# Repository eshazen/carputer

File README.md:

# carputer

Car computer with display and GPS in DIN enclosure

Proposed functions:

* Clock (updated by GPS)
* Nearest town and potentially other geographical features
* Outside temperature

Front panel would have a display, a couple of buttons/knobs
and a USB plug for power from the stereo plus software updates
using Arduino boot loader.

See (Data/README.md)[Data/README.md] for data details and ideas.

## Implementation notes

On the MKR Zero board, there are only a few pins which can be used for
interrupts.  See
[docs](https://docs.arduino.cc/language-reference/en/functions/external-interrupts/attachInterrupt/).
These pins are: 0, 1, 4, 5, 6, 7, 8, 9, A1, A2.

Unfortunately the encoder is connected to 11 and 12.  Pin 7 is unused,
but one interrupt doesn't do the trick.

So far no luck getting timer interrupts to work on the MKR zero.
Best bet seems to be the `Adafruit_ZeroTimer` but even though the
example works it seems to crash when trying to run e.g. SPI after setup.

## User Interface

First version displays 3 lines of nearest towns, with a status
line below with GMT time, GPS status and number of satellites.
Controls not implemented yet.

### Enhancements:

**V3.x**

* Hierarchy of search (state first, then state-specific towns?)
* Simple UI (button/knob to enable/disable debug mode)

**Other**

* Categories of POI, selected by knob
  <br>with timeout to return to town display?
* Clock time in local time zone (how to determine time zone?)
* Analog clock display
* Scrolling of long place names?

## Resources

See [https://github.com/eshazen/town_ident](https://github.com/eshazen/town_ident)
for a preliminary version based on ATMega328.

## Hardware

* **CPU** - Arduino MKR Zero.  SAMD21 cpu with 256k flash and 32k ram.  32-bit M0 core at 48MHz.
* **Display** - OLED with 3.12 inch 256x64 display.  Amazon:  [https://a.co/d/5zJTbLo](https://a.co/d/5zJTbLo)
* **GPS** - NEO-6M module (Amazon: [link](https://a.co/d/gSQQ6ZD).  The NEO-7M is a higher-performance replacement
* **Antenna** - Bingfu Waterproof "Active" GPS antenna SMA (Amazon: [link](https://a.co/d/aN1YYik).

### Display details

Ordered this 3.12" OLED with 16-pin connector from 
Asked ChatGPT for a pinout and it came up with [this](https://chatgpt.com/share/68c1a13d-e6dc-8000-bd67-d93712c7cb28).

Also see [ER-OLEDM028-1_Interfacing.pdf](Docs/ER-OLEDM028-1_Interfacing.pdf).

Link to
[Datasheet](https://newhavendisplay.com/content/specs/NHD-3.12-25664UCY2.pdf) for DigiKey version.

Beeped out from ours

| Function   | Pin |   | Pin | Function   |
|------------|-----|---|-----|------------|
| GND        | 1   |   | 2   | ?VCC       |
| ?          | 3   |   | 4   | D0 (SCLK?) |
| D1 (SDIN?) | 5   |   | 6   | D2         |
| D3         | 7   |   | 8   | D4         |
| D5         | 9   |   | 10  | D6         |
| D7         | 11  |   | 12  | E/RD       |
| R/W        | 13  |   | 14  | DC         |
| RES        | 15  |   | 16  | CS         |
|            |     |   |     |            |

See https://www.hicenda.com/product/312-inch-oled-module-01.html

Finally, referring to a datasheet: https://docs.rs-online.com/6267/0900766b8162af09.pdf
for the display itself with 30 pin flex, we can wring out the pinout with a meter.

Library candidates:

* [SSD1322_for_Adafruit_GFX](https://github.com/venice1200/SSD1322_for_Adafruit_GFX)
* [SSD1322_OLED_library](https://github.com/wjklimek1/SSD1322_OLED_library)

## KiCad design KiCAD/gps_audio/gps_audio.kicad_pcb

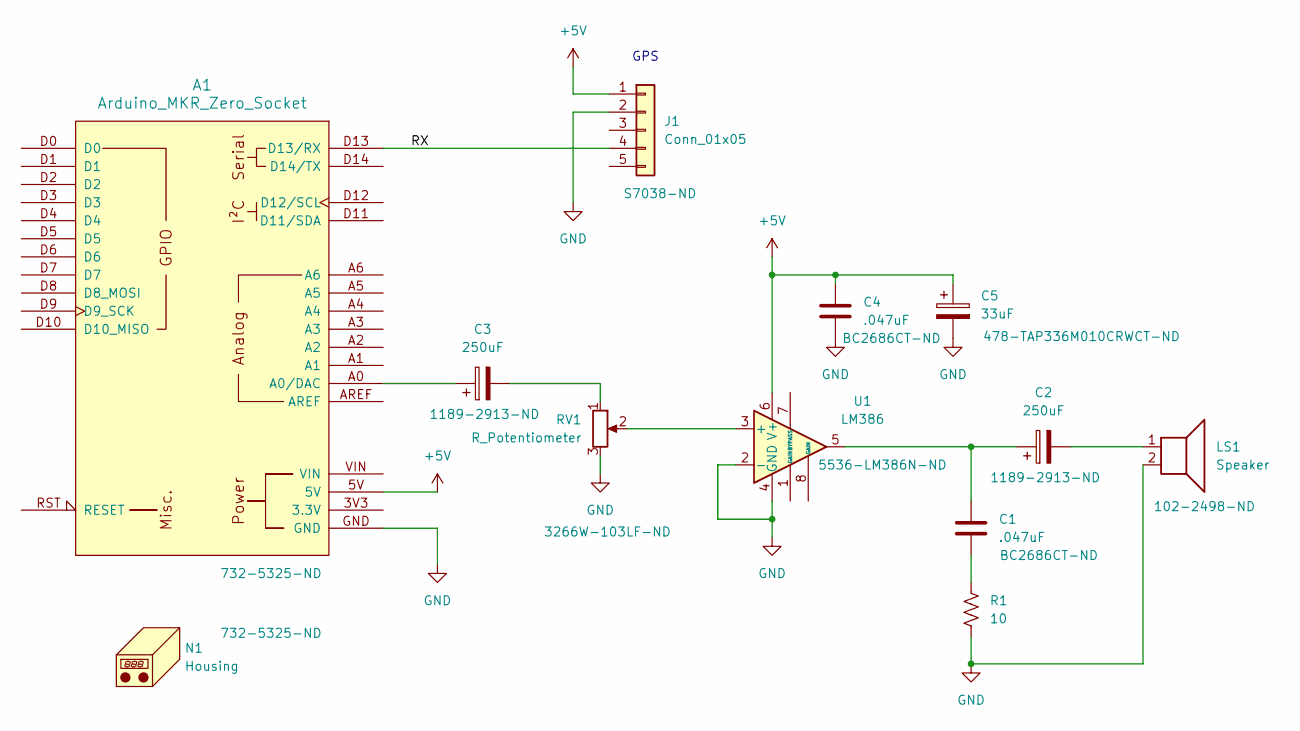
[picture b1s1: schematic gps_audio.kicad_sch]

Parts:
A1: Arduino_MKR_Zero_Socket
C1, C4: .047uF; C_Disc_D7.0mm_W2.5mm_P5.00mm
C2, C3: 250uF; CP_Radial_D6.3mm_P2.50mm
C5: 33uF; CP_Radial_Tantal_D4.5mm_P5.00mm
J1: Conn_01x05; gps_module
LS1: Speaker; CVS-1508_CUD
N1: Housing
R1: 10; R_Axial_DIN0207_L6.3mm_D2.5mm_P10.16mm_Horizontal
RV1: R_Potentiometer; Potentiometer_Bourns_3266W_Vertical
U1: LM386; DIP-8_W7.62mm

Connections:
+5V: A1.5V, C4.1, C5.1, J1.1, U1.6 (V+)
/RX: A1.D13 (D13/RX), J1.4
GND: A1.GND, C4.2, C5.2, J1.2, LS1.2, R1.2, RV1.3, U1.2 (-), U1.4 (GND)
unnamed: A1.A0 (A0/DAC), C3.1
unnamed: C1.1, C2.1, U1.5
unnamed: C1.2, R1.1
unnamed: C2.2, LS1.1
unnamed: C3.2, RV1.1
unnamed: RV1.2, U1.3 (+)

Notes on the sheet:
GPS

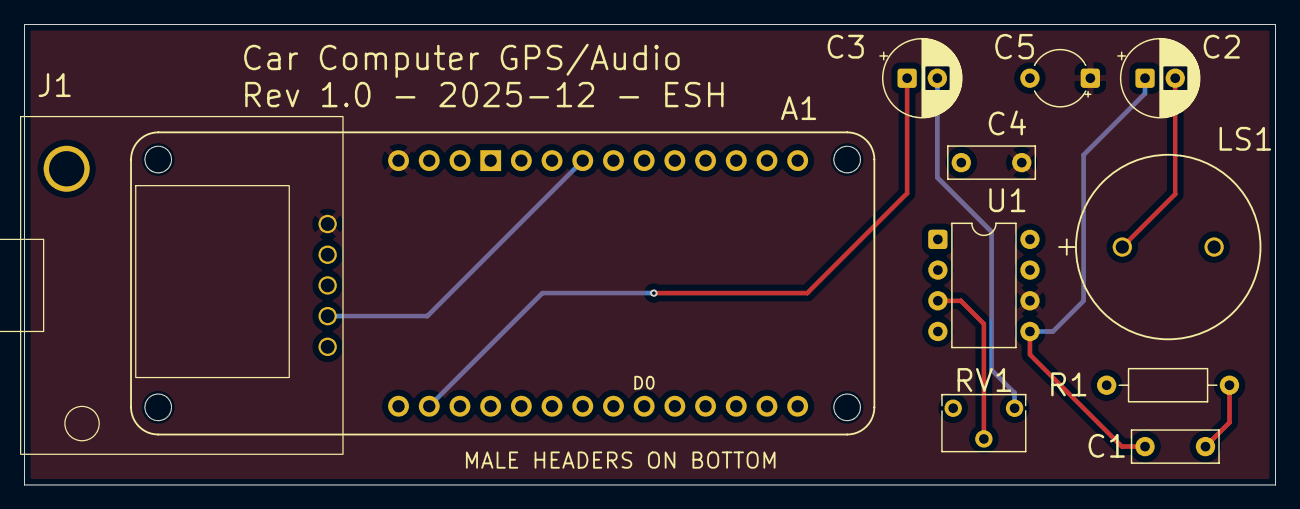
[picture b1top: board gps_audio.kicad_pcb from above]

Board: 2 copper layers, 103.5 x 38.1 mm, 11 parts (0 on the bottom side), 9 nets.

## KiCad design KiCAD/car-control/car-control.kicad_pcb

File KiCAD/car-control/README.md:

# ECOS for rev 1

* R3, R4 too small, LEDs way too bright!
  * Change to 3.3k
* Tx and Rx reversed? (works fine with 1:1 cable on SCOS board though)

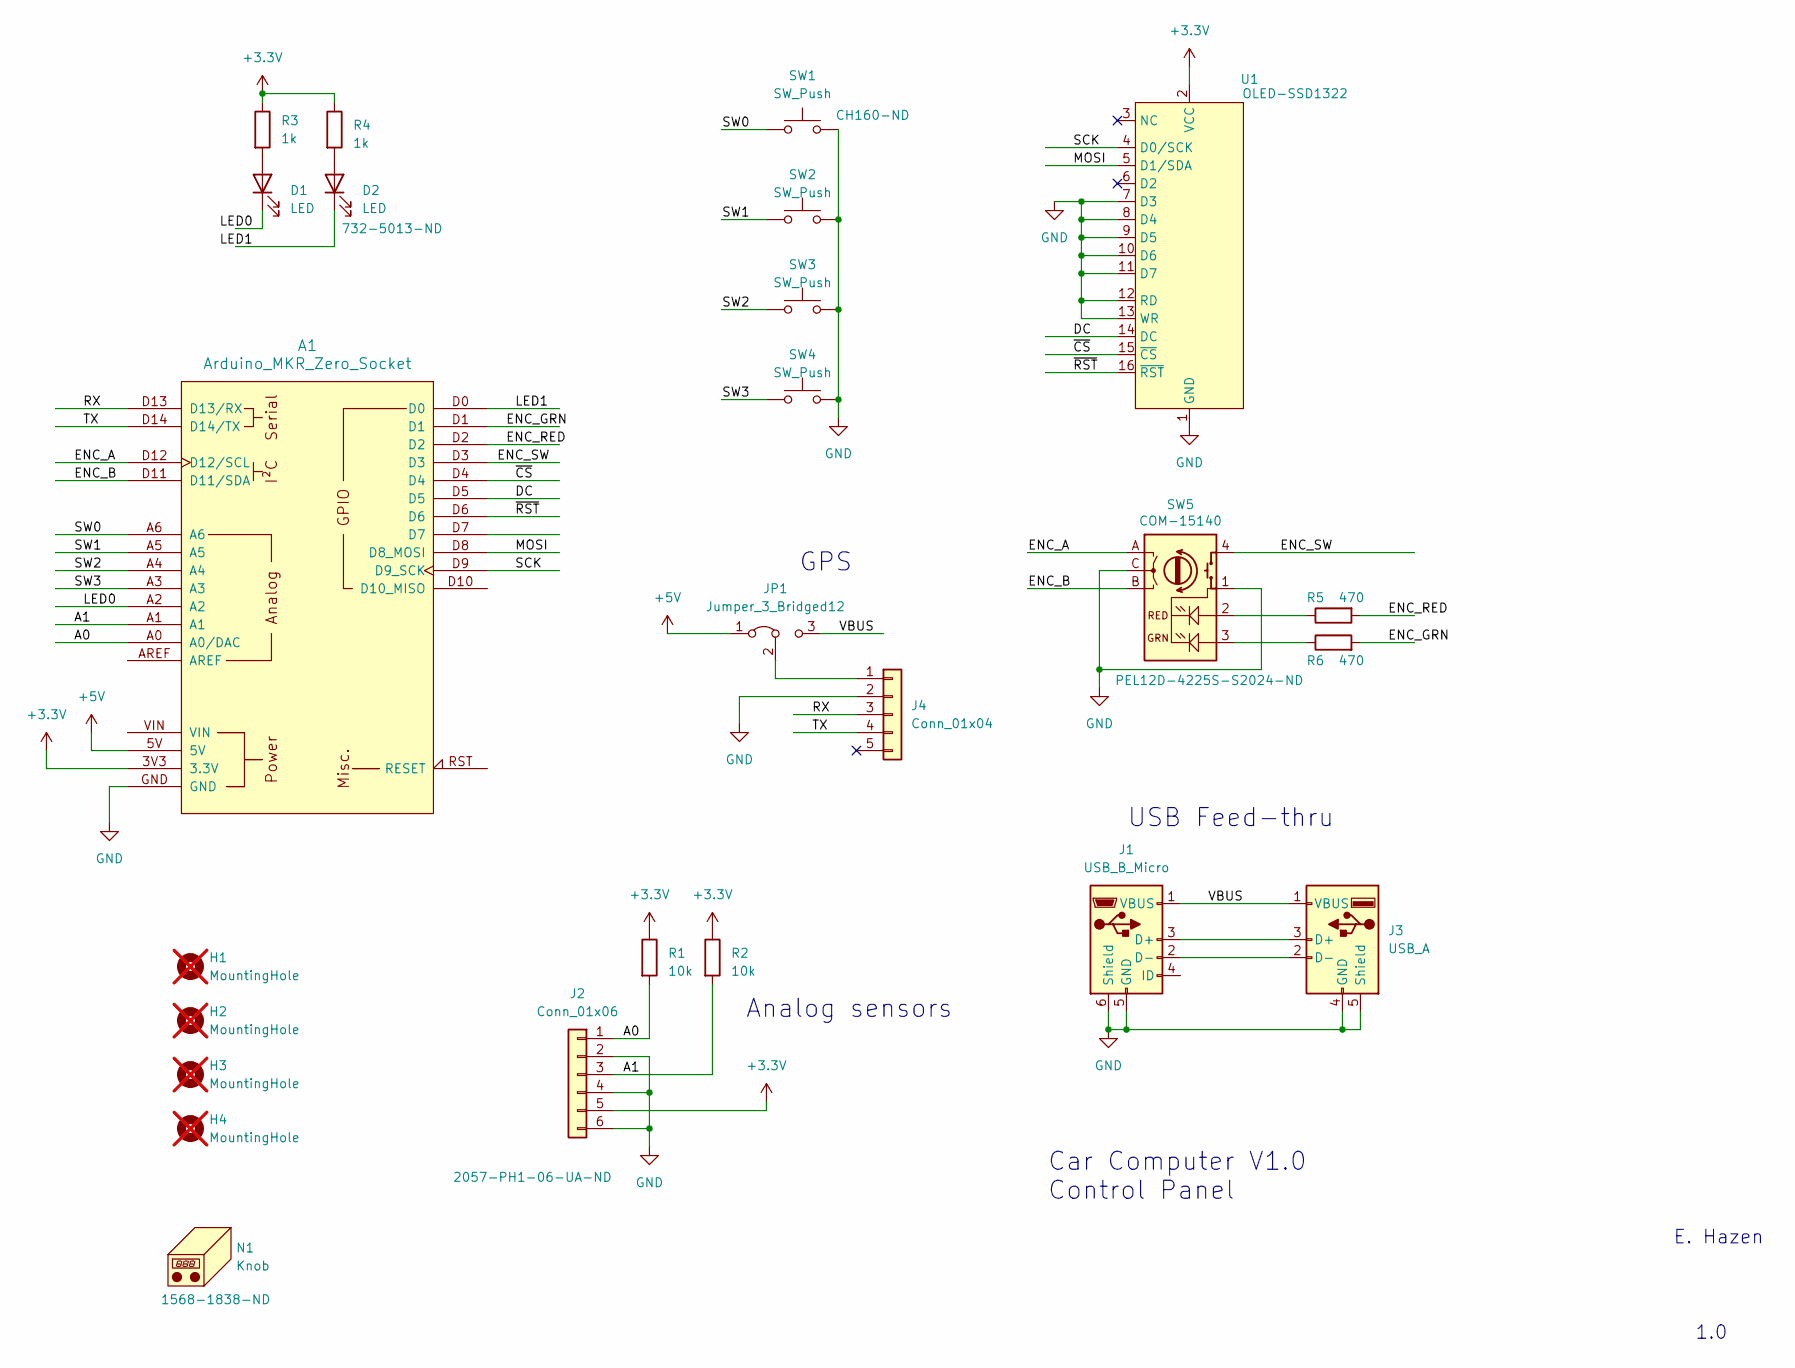
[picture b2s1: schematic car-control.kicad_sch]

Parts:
A1: Arduino_MKR_Zero_Socket
D1, D2: LED; LED_D3.0mm
H1, H2, H3, H4: MountingHole; mtg_hole_4-40; not fitted
J1: USB_B_Micro; CONN_USB3131-30-0230-A_GCT
J2: Conn_01x06; PinHeader_1x06_P2.54mm_Vertical
J3: USB_A; CONN_USB-A-S-VT_ADM
J4: Conn_01x04; PinSocket_1x05_P2.54mm_Vertical
JP1: Jumper_3_Bridged12; PinHeader_1x03_P2.54mm_Vertical
N1: Knob
R1, R2: 10k; R_1206_3216Metric_Pad1.30x1.75mm_HandSolder
R3, R4: 1k; R_1206_3216Metric_Pad1.30x1.75mm_HandSolder
R5, R6: 470; R_1206_3216Metric_Pad1.30x1.75mm_HandSolder
SW1, SW2, SW3, SW4: SW_Push; SW_Cherry_MX_1.00u_PCB
SW5: COM-15140; rotary-RG-3D
U1: OLED-SSD1322; OLED_312_16pin

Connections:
+3.3V: A1.3V3 (3.3V), J2.5, R1.1, R2.1, R3.1, R4.1, U1.2 (VCC)
+5V: A1.5V, JP1.1 (A)
/A0: A1.A0 (A0/DAC), J2.1, R1.2
/A1: A1.A1, J2.3, R2.2
/DC: A1.D5, U1.14 (DC)
/ENC_A: A1.D12 (D12/SCL), SW5.A
/ENC_B: A1.D11 (D11/SDA), SW5.B
/ENC_GRN: A1.D1, R6.2
/ENC_RED: A1.D2, R5.2
/ENC_SW: A1.D3, SW5.4 (S1)
/LED0: A1.A2, D1.1 (K)
/LED1: A1.D0, D2.1 (K)
/MOSI: A1.D8 (D8_MOSI), U1.5 (D1/SDA)
/RX: A1.D13 (D13/RX), J4.3
/SCK: A1.D9 (D9_SCK), U1.4 (D0/SCK)
/SW0: A1.A6, SW1.1
/SW1: A1.A5, SW2.1
/SW2: A1.A4, SW3.1
/SW3: A1.A3, SW4.1
/TX: A1.D14 (D14/TX), J4.4
/VBUS: J1.1 (VBUS), J3.1 (VBUS), JP1.3 (B)
/~CS: A1.D4, U1.15 (~CS)
/~RST: A1.D6, U1.16 (~RST)
GND: A1.GND, J1.5 (GND), J1.6 (Shield), J2.2, J2.4, J2.6, J3.4 (GND), J3.5 (Shield), J4.2, SW1.2, SW2.2, SW3.2, SW4.2, SW5.1 (S2), SW5.C, U1.1 (GND), U1.7 (D3), U1.8 (D4), U1.9 (D5), U1.10 (D6), U1.11 (D7), U1.12 (RD), U1.13 (WR)
unnamed: D1.2 (A), R3.2
unnamed: D2.2 (A), R4.2
unnamed: J1.3 (D+), J3.3 (D+)
unnamed: J1.2 (D-), J3.2 (D-)
unnamed: J4.1, JP1.2 (C)
unnamed: R6.1, SW5.3 (GREEN)
unnamed: R5.1, SW5.2 (RED)

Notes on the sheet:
E. Hazen
GPS
USB Feed-thru
Car Computer V1.0 Control Panel
1.0
Analog sensors

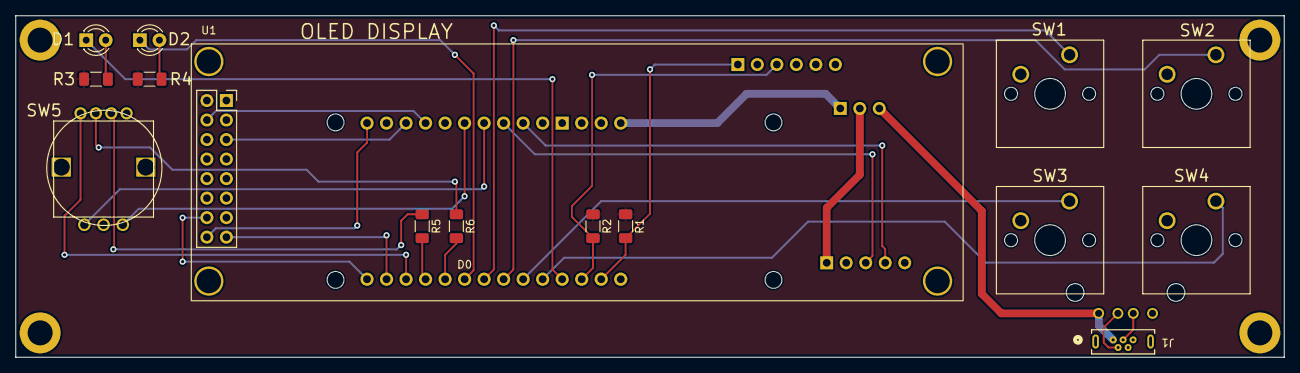
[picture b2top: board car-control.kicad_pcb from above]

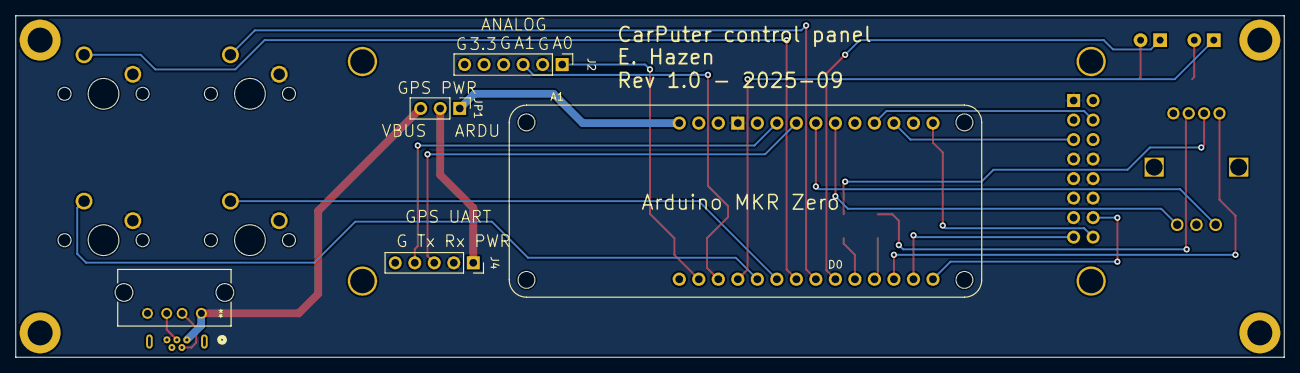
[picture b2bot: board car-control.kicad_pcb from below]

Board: 2 copper layers, 165.1 x 44.5 mm, 24 parts (5 on the bottom side), 31 nets.

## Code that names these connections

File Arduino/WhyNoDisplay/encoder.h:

#ifndef ENCODER_H_INCLUDED
#define ENCODER_H_INCLUDED

#include <RotaryEncoder.h>

#define ENC_A 12
#define ENC_B 11
#define ENC_GRN 1
#define ENC_RED 2
#define ENC_SW 3

RotaryEncoder *encoder = nullptr;

void encoder_setup() {
  pinMode( ENC_A, INPUT_PULLUP);
  pinMode( ENC_B, INPUT_PULLUP);
  pinMode( ENC_SW, INPUT_PULLUP);
  pinMode( ENC_RED, OUTPUT);
  pinMode( ENC_GRN, OUTPUT);

  encoder = new RotaryEncoder( ENC_A, ENC_B, RotaryEncoder::LatchMode::FOUR3);
}


#endif

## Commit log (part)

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2025-09-10 create repo, upload some OPs models
2025-09-10 documentation
2025-09-14 working on case
2025-09-15 working on mount
2025-09-15 working on front panel model
2025-09-15 rename KiCAD project
2025-09-15 working on PCB
2025-09-15 working on layout
2025-09-16 working on layout, move USB
2025-09-20 PCB done?
2025-09-20 latest mount
2025-09-22 updates to case
2025-09-22 standoffs
2025-09-22 standoffs, final? gerbers
2025-09-23 case
2025-09-25 software
2025-09-26 initial software, fix layout
2025-09-26 GPS test display
2025-09-26 PCB V1.0 as built
2025-09-27 working on data extraction
2025-09-27 working on data
2025-09-29 working on grid
2025-09-29 save CSV files!
2025-09-29 adding back CSV files, working index?
2025-09-29 working on embedded code simulation
2025-09-29 debugging simulation
2025-09-30 working with qsort
2025-09-30 working on FindLocs.ino
2025-09-30 FindLocs.ino compiles!
2025-10-01 FindLocs serial working
2025-10-01 FindLocs not compiling
2025-10-01 Old FindLocs moved to FindLocsSerial, FindLocs compiles now
2025-10-02 works (is) but crashes after 3 updates
2025-10-05 seems to work, needs display work
2025-10-05 tweaking the display
2025-10-06 fix lip on front panel
2025-10-06 tweaking front panel
2025-10-08 tweaking the dimensions
2025-10-14 last enclosure tweaks
2025-10-14 update panel and box
2025-10-15 label.scad has text labels on front panel
2025-10-16 readme, diners
2025-10-19 working on V2 software
2025-10-23 ControlTest working with interrupts
2025-10-23 shaft encoder readout in FindLocs2
2025-10-23 working on groups
2025-10-23 need a separate grid for each location type
2025-11-08 readme
2025-11-09 shapefile stuff
2025-11-17 restore FindLocs2
2025-11-19 rtrees
2025-11-19 tweaks to shape
2025-11-19 working on r-trees
2025-11-20 working on file tree
2025-11-24 debugging with fake data
2025-11-24 work
2025-11-25 add search to grid_eval
2025-11-27 starting re-work for multi-part files
2025-11-30 about to re-work lat/lon storage
2025-12-01 maybe some bugs in new file format
2025-12-02 working on file format
2025-12-11 fix some bugs
2025-12-11 fixed bug, need to work on merge
2025-12-14 initial working? desktop version
2025-12-15 debugging the arduino
2025-12-15 initial arduino version working
2025-12-18 first working lookup/display in ShapeDisplay
2025-12-18 no serial option
2025-12-19 ShapeDisplay working with GPS
2025-12-19 Rev 1.0 shape display
2025-12-19 readme, notes
2025-12-20 Audio PCB, download TZ shapefile, update notes
2025-12-22 version 1.2
2025-12-23 Rev 1.3 - add Boston neighborhoods
2025-12-23 add some more databases
2025-12-24 WhyNoDisplay working with timer and oled
2025-12-25 starting rework
2025-12-28 working on brute force search for ios
2025-12-28 clean
2026-01-12 starting work on sound
2026-01-14 add some dims
2026-01-15 Add speaker holder proto
2026-01-18 V2.0 with sound as ShapeDisplay2
2026-01-24 Deploy version with sound
2026-04-17 working on MA towns
2026-04-18 Add MA towns
